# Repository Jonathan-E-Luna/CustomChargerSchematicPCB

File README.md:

# CustomChargerSchematicPCB
During my groups capstone, I was in charge of the PCB design for all custom hardware components utilized. The boards are subdivided into three main catagories
1) Power boards- These boards are Switching Regulators designed to power the microcontronller, Current Switch Board (Will be mentioned later) and a raspberry pi module. Since all power boards use the same switch regulator IC, only one is shown
2) MCU Board - This board houses an ESP-32 Microcontroller that will controll the Current/Voltage measurement IC (INA260) and the Load Switch TPS22918
3) Current Switch Board - Houses the INA260 and TPS22918 that will take current from the 5V regulator and deliver power to a load.

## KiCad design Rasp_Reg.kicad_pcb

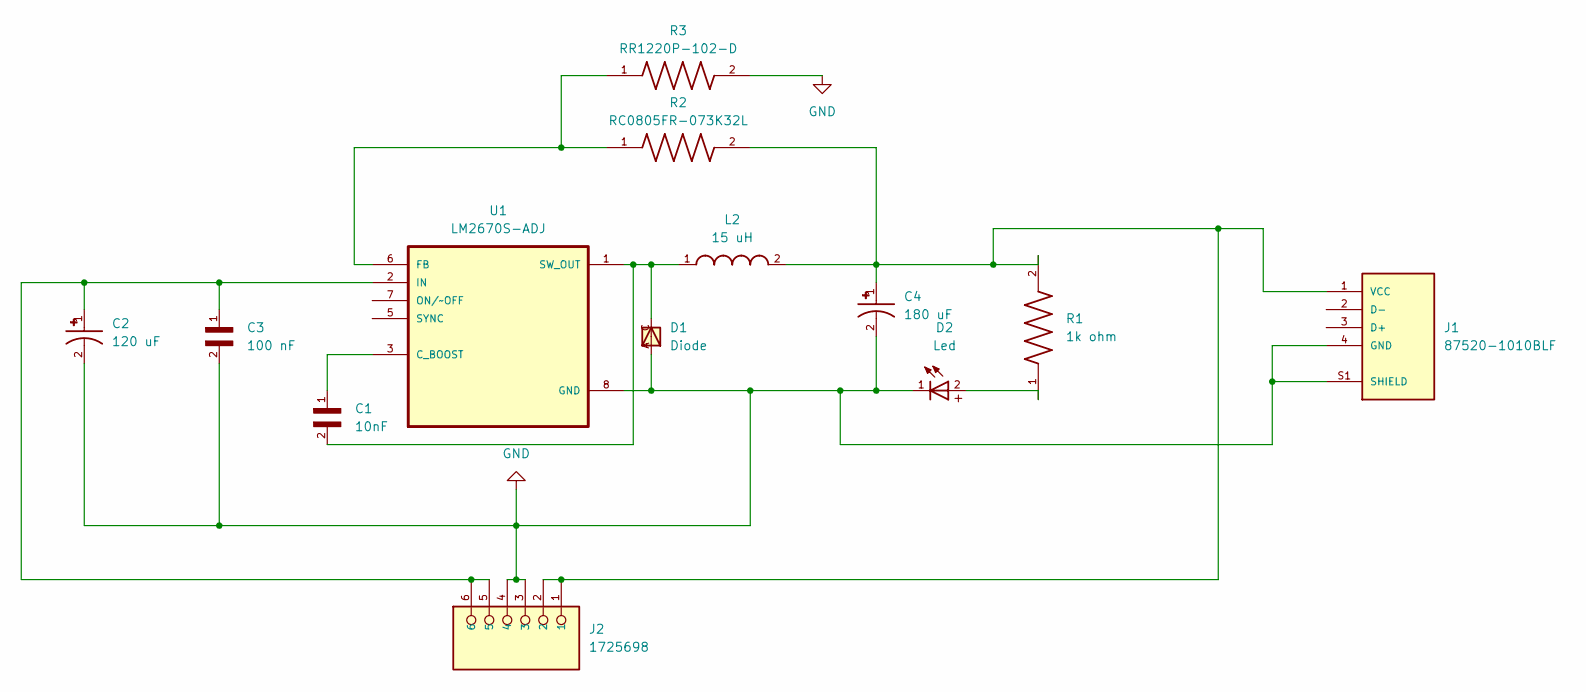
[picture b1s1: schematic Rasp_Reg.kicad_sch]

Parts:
C1: 10nF; CAPC2012X75N
C2: 120 uF; CAP_20SVPF120M; PARTREV 28-Jun-19
C3: 100 nF; CAPC2012X94N
C4: 180 uF; CAP_16SVPE180M; PARTREV 05-Mar-21
D1: Diode; SMB
D2: Led; WL-SMCW_0805
J1: 87520-1010BLF; AMPHENOL_87520-1010BLF; PARTREV AR
J2: 1725698; PHOENIX_1725698; PARTREV 03.03.2021
L2: 15 uH; INDP125125X785N
R1: 1k ohm; RESC2012X50N
R2: RC0805FR-073K32L; RESC2012X60N
R3: RR1220P-102-D; RESC2012X50N
U1: LM2670S-ADJ; TO127P1435X464-8N

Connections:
GND: C2.2, C3.2, C4.2, D1.A, D2.1, J1.4 (GND), J1.S1 (SHIELD), J1.S2 (SHIELD), J2.3, J2.4, R3.2, U1.4 (GND), U1.8 (GND)
unnamed: D2.2, R1.1
unnamed: C4.1, J1.1 (VCC), J2.1, J2.2, L2.2, R1.2, R2.2
unnamed: C1.1, U1.3 (C_BOOST)
unnamed: R2.1, R3.1, U1.6 (FB)
unnamed: C2.1, C3.1, J2.5, J2.6, U1.2 (IN)
unnamed: C1.2, D1.C, L2.1, U1.1 (SW_OUT)

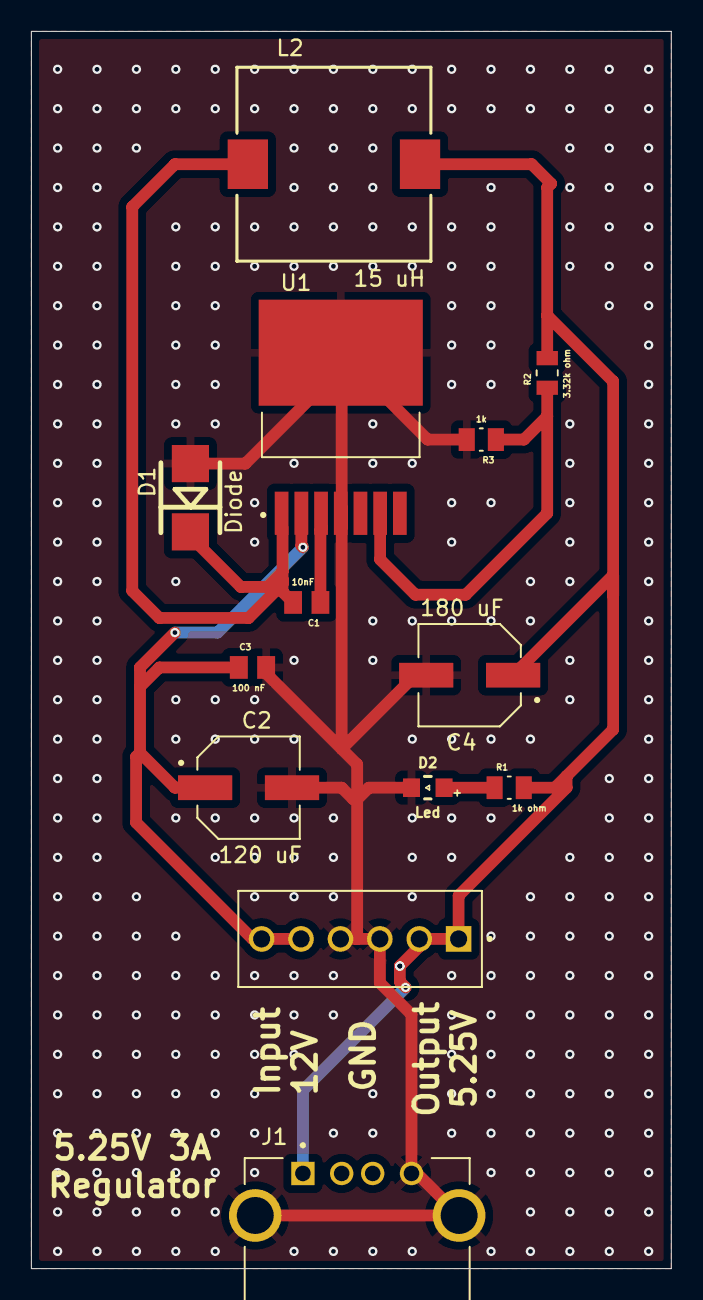
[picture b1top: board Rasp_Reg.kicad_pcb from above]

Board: 2 copper layers, 41.2 x 79.8 mm, 13 parts (0 on the bottom side), 7 nets.

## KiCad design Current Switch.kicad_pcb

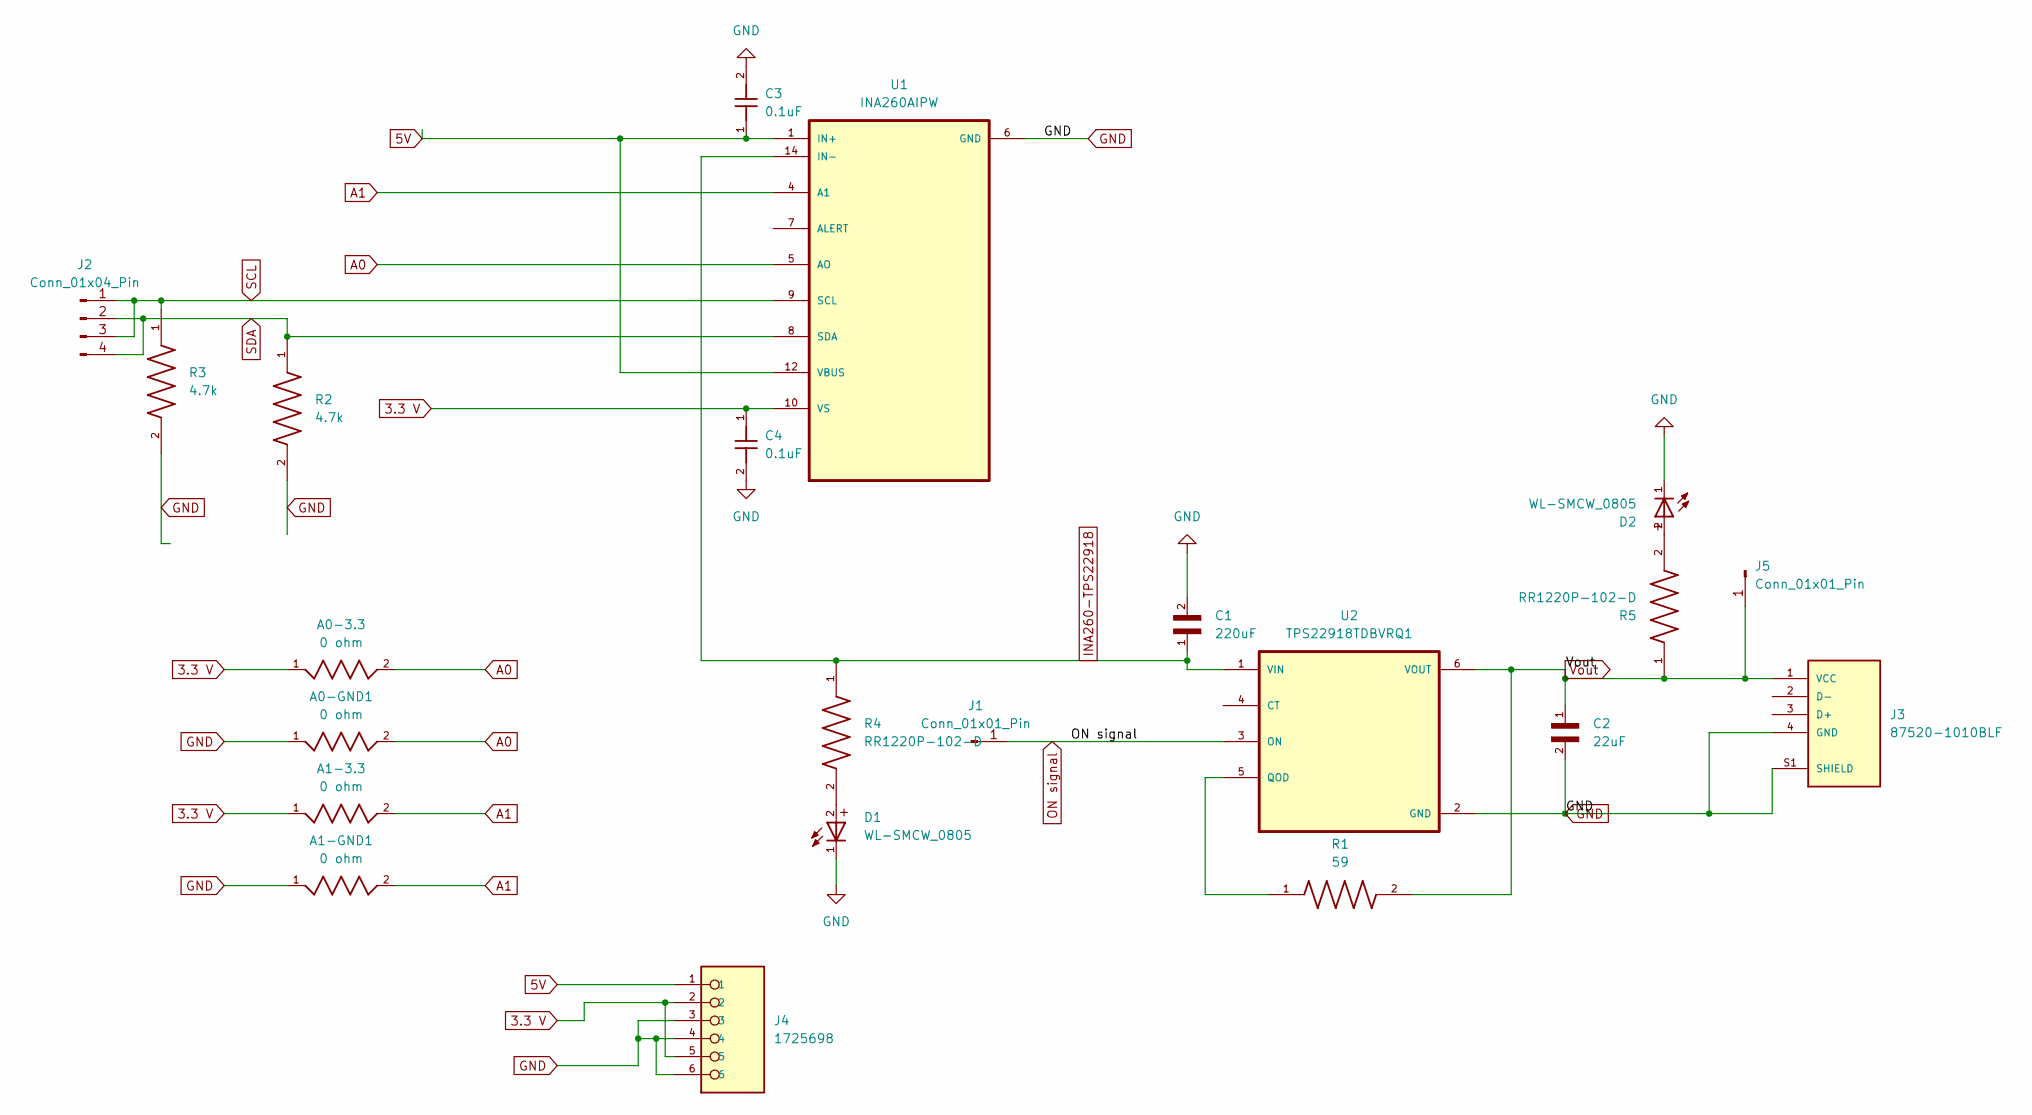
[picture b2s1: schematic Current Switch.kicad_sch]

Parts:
A0-3.3, A0-GND1, A1-3.3, A1-GND1: 0 ohm; RESC2012X60N; PARTREV V.12
C1: 220uF; CAPC3216X190N
C2: 22uF; CAPC2012X140N
C3, C4: 0.1uF; CAPC2012X88N
D1, D2: WL-SMCW_0805
J1, J5: Conn_01x01_Pin; PinHeader_1x01_P2.54mm_Vertical
J2: Conn_01x04_Pin; PinHeader_1x04_P2.54mm_Vertical
J3: 87520-1010BLF; AMPHENOL_87520-1010BLF; PARTREV AR
J4: 1725698; PHOENIX_1725698; PARTREV 03.03.2021
R1: 59; RESC2012X50N
R2, R3: 4.7k; RES_ERA6AEB472V; PARTREV 3/1/2020
R4, R5: RR1220P-102-D; RESC2012X50N
U1: INA260AIPW; SOP65P640X120-16N
U2: TPS22918TDBVRQ1; SOT95P280X145-6N

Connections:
3.3 V: A0-3.3.1, A1-3.3.1, C4.1, J4.2, J4.5, U1.10 (VS)
5V: C3.1, J4.1, U1.1 (IN+), U1.2 (IN+), U1.3 (IN+), U1.12 (VBUS)
A0: A0-3.3.2, A0-GND1.2, U1.5 (AO)
A1: A1-3.3.2, A1-GND1.2, U1.4 (A1)
GND: A0-GND1.1, A1-GND1.1, C1.2, C2.2, C3.2, C4.2, D1.1, D2.1, J3.4 (GND), J3.S1 (SHIELD), J3.S2 (SHIELD), J4.3, J4.4, J4.6, R2.2, R3.2, U1.6 (GND), U1.11 (GND), U2.2 (GND)
INA260-TPS22918: C1.1, R4.1, U1.14 (IN-), U1.15 (IN-), U1.16 (IN-), U2.1 (VIN)
unnamed: D1.2, R4.2
unnamed: D2.2, R5.2
unnamed: R1.1, U2.5 (QOD)
ON signal: J1.1, U2.3 (ON)
SCL: J2.1, J2.3, R3.1, U1.9 (SCL)
SDA: J2.2, J2.4, R2.1, U1.8 (SDA)
Vout: C2.1, J3.1 (VCC), J5.1, R1.2, R5.1, U2.6 (VOUT)

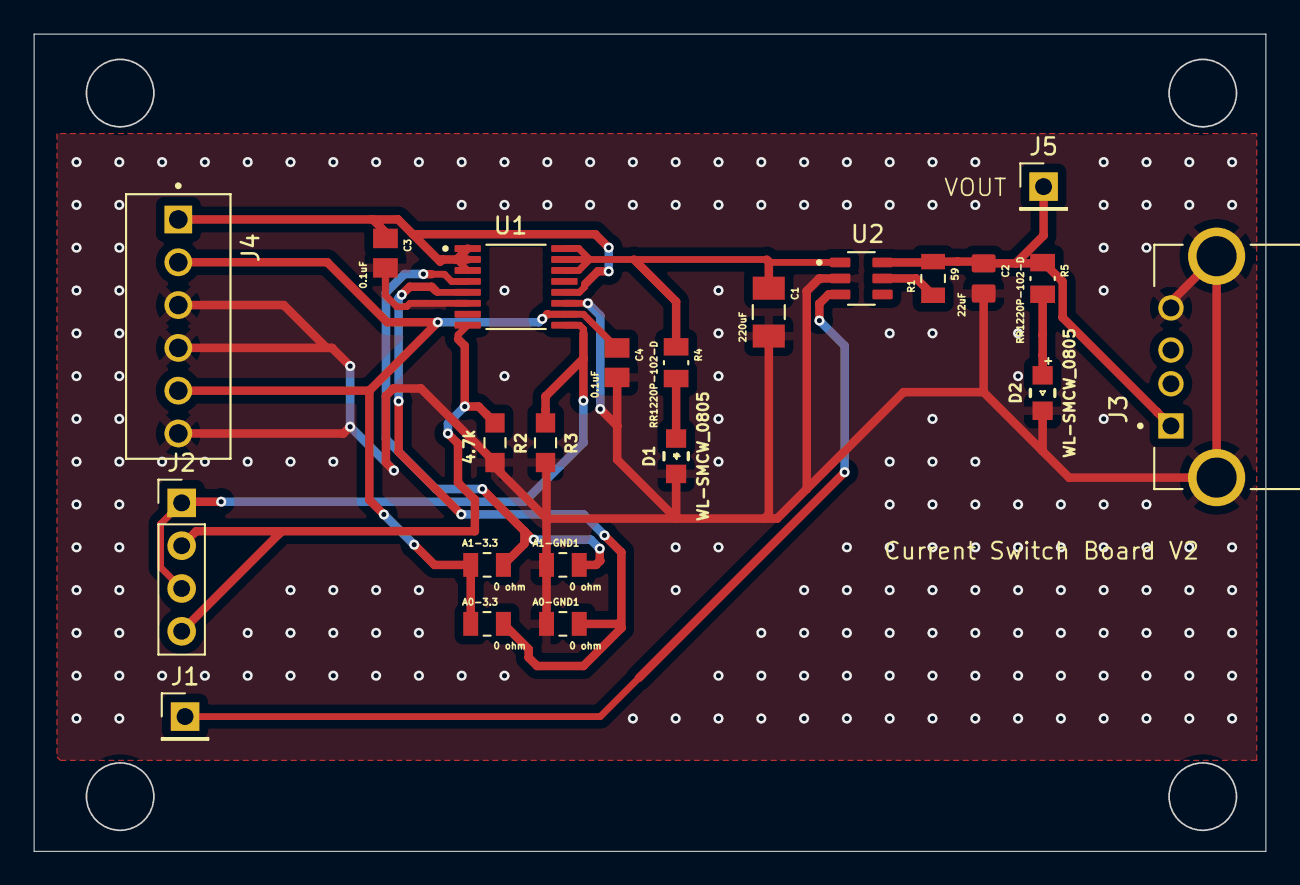
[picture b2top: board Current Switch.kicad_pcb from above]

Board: 2 copper layers, 73.1 x 48.5 mm, 22 parts (0 on the bottom side), 13 nets.

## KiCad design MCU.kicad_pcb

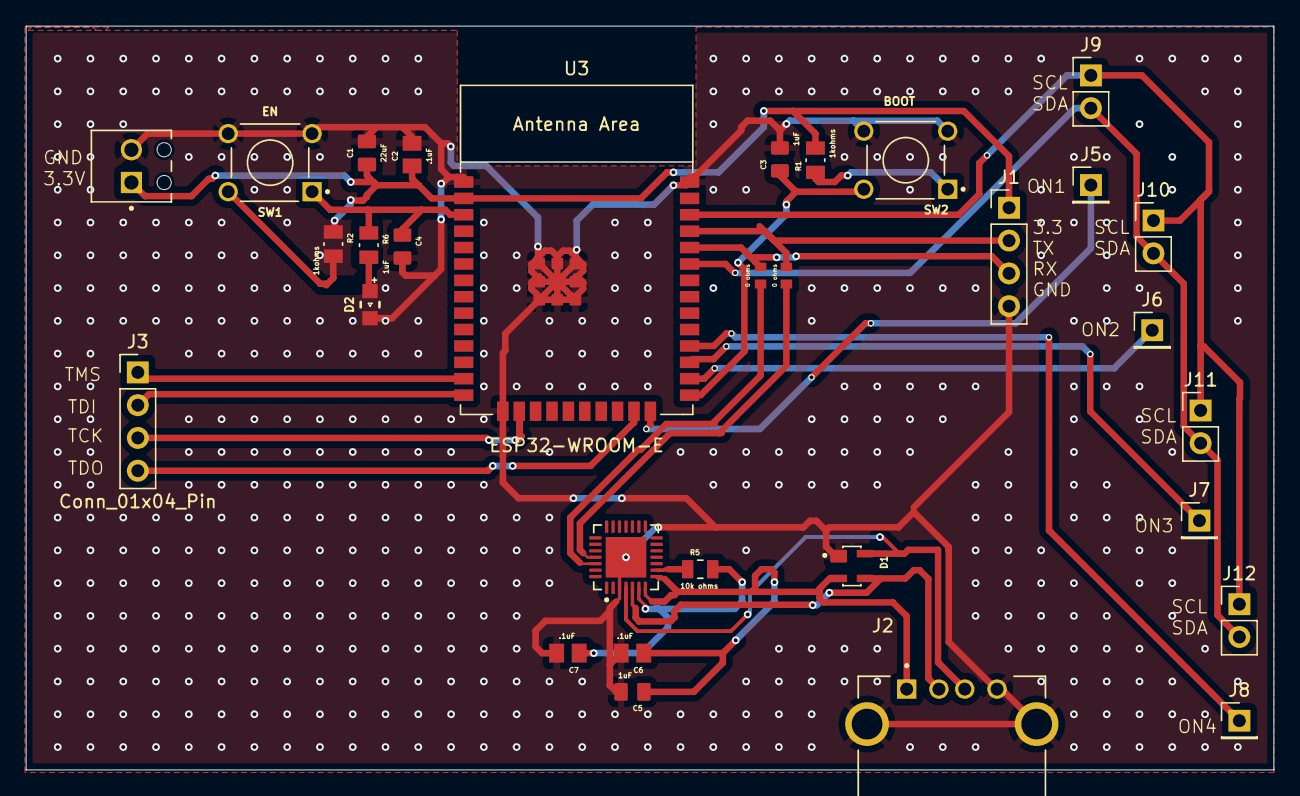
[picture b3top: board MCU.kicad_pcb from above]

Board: 2 copper layers, 96.7 x 57.6 mm, 31 parts (0 on the bottom side), 26 nets.

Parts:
C1: 22uF; CAPC2012X140N
C2, C6, C7: .1uF; CAPC2012X88N
C3, C4, C5: 1uF; CAPC2012X135N
D1: SP0503BAHTG; SOT143
D2: WL-SMCW_0805
J1, J3: Conn_01x04_Pin; PinHeader_1x04_P2.54mm_Vertical
J2: 87520-1010BLF; AMPHENOL_87520-1010BLF
J4: 1725656; PHOENIX_1725656
J5: ON1; PinHeader_1x01_P2.54mm_Vertical
J6: ON2; PinHeader_1x01_P2.54mm_Vertical
J7: ON3; PinHeader_1x01_P2.54mm_Vertical
J8: ON4; PinHeader_1x01_P2.54mm_Vertical
J9: ON1; PinHeader_1x02_P2.54mm_Vertical
J10, J11, J12: Conn_01x02_Pin; PinHeader_1x02_P2.54mm_Vertical
R1, R2, R6: 1kohms; RESC2012X50N
R3, R4: 0 ohms; RESC1005X40
R5: 10k ohms; RESC2012X60N
SW1: EN; SW_1825910-6-4
SW2: BOOT; SW_1825910-6-4
U2: CP2102-GM; QFN50P500X500X100-29N
U3: ESP32-WROOM-E; ESP32-WROOM-32E

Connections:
BOOT: C3.1, SW2.2, U3.25 (GPIO0/BOOT/ADC2_CH1)
EN: C4.1, R6.1, SW1.1, U3.3 (EN/CHIP_PU)
GND: C1.2, C2.2, C3.2, C4.2, C5.2, C6.2, C7.2, D1.1, D2.1, J1.4, J2.4 (GND), J2.S1 (SHIELD), J2.S2 (SHIELD), J4.2, SW1.3, SW1.4, SW2.3, SW2.4, U2.3 (GND), U2.29 (GND), U3.1 (GND), U3.15 (GND), U3.38 (GND), U3.39 (GND_THERMAL)
unnamed: D2.2, R6.2
unnamed: D1.4, J2.3 (D+), U2.4 (D+)
unnamed: D1.3, J2.2 (D-), U2.5 (D–)
unnamed: R1.1, SW2.1
unnamed: R2.2, SW1.2
unnamed: R3.2, U2.25 (RXD)
unnamed: R4.1, U2.26 (TXD)
unnamed: C7.1, R5.2, U2.6 (VDD)
unnamed: R5.1, U2.9 (~RST)
ON 1: J5.1, U3.24 (ADC2_CH2/GPIO2)
ON 2: J6.1, U3.26 (ADC2_CH0/GPIO4)
ON 3: J7.1, U3.27 (GPIO16)
ON 4: J8.1, U3.28 (GPIO17)
RX: J1.3, R4.2, U3.34 (U0RXD/GPIO3)
SCL: J9.1, J10.1, J11.1, J12.1, U3.36 (GPIO22)
SDA: J9.2, J10.2, J11.2, J12.2, U3.33 (GPIO21)
TCK: J3.3, U3.16 (MTCK/GPIO13/ADC2_CH4)
TDI: J3.2, U3.14 (MTDI/GPIO12/ADC2_CH5)
TDO: J3.4, U3.23 (MTDO/GPIO15/ADC2_CH3)
TMS: J3.1, U3.13 (MTMS/GPIO14/ADC2_CH6)
TX: J1.2, R3.1, U3.35 (U0TXD/GPIO1)
VBUS: C5.1, C6.1, D1.2, J2.1 (VCC), U2.7 (REGIN), U2.8 (VBUS)
VDD33: C1.1, C2.1, J1.1, J4.1, R1.2, R2.1, U3.2 (3V3)

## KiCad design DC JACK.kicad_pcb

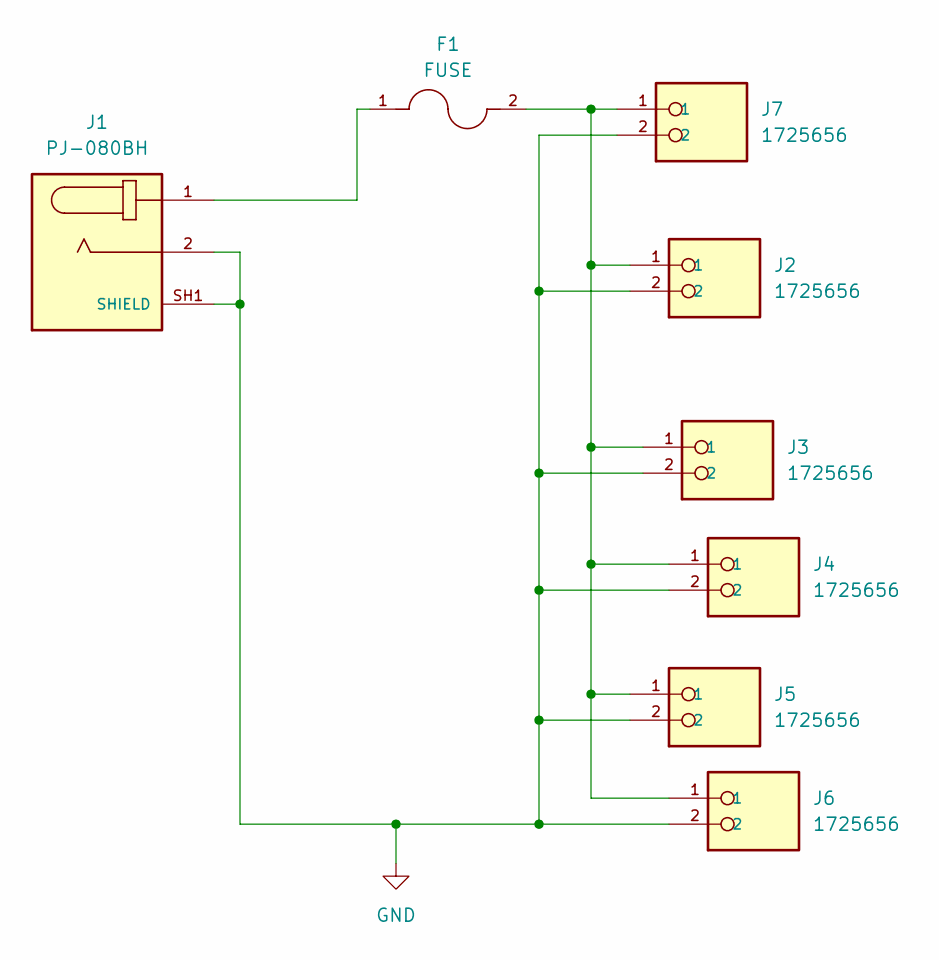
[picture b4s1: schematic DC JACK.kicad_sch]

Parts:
F1: FUSE; FUSC6125X279N; PARTREV 0679H Apr2019
J1: PJ-080BH; CUI_PJ-080BH; PARTREV 1.04
J2, J3, J4, J5, J6, J7: 1725656; PHOENIX_1725656; PARTREV 03.03.2021

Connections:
GND: J1.2, J1.SH1 (SHIELD), J1.SH2 (SHIELD), J1.SH3 (SHIELD), J1.SH4 (SHIELD), J2.2, J3.2, J4.2, J5.2, J6.2, J7.2
unnamed: F1.1, J1.1
unnamed: F1.2, J2.1, J3.1, J4.1, J5.1, J6.1, J7.1

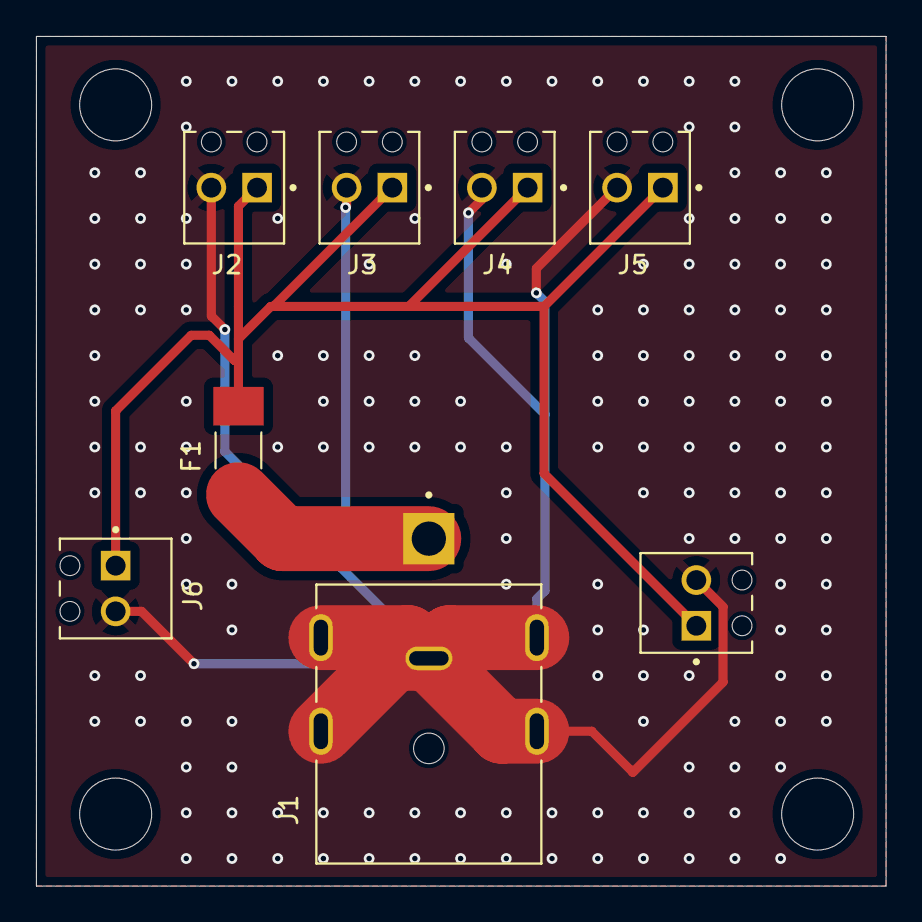
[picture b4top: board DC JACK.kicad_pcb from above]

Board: 2 copper layers, 47.2 x 47.2 mm, 8 parts (0 on the bottom side), 3 nets.

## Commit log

2026-03-20 Enhance README with detailed PCB design categories
    Expanded description of PCB design and its components.
2026-03-20 Update description of Powerboard schematics
2026-03-20 Add files via upload
    All Schematics related to power regulation
2026-03-20 Update README with additional details on power boards
    Clarified description of power boards in README.
